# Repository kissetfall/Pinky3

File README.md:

# Pinky3

Pinky3 fork with rotary encoders and kailh hotswaps for thumb row.
This is a WIP, but it's already works great for daily use.

No top/bottom plates are currently available for this board, but it works nice without them.

## Layout

## Firmware

Copy the contents of keymap directory in your qmk/keyboards/pinky/3/keymaps

## TODOs

- [ ] Full choc hotswap support
- [ ] Rework of top, bottom plates, screw holes position.
- [ ] Led strip support
- [ ] Renaming keyboard
- [ ] Build guides, bom, etc.

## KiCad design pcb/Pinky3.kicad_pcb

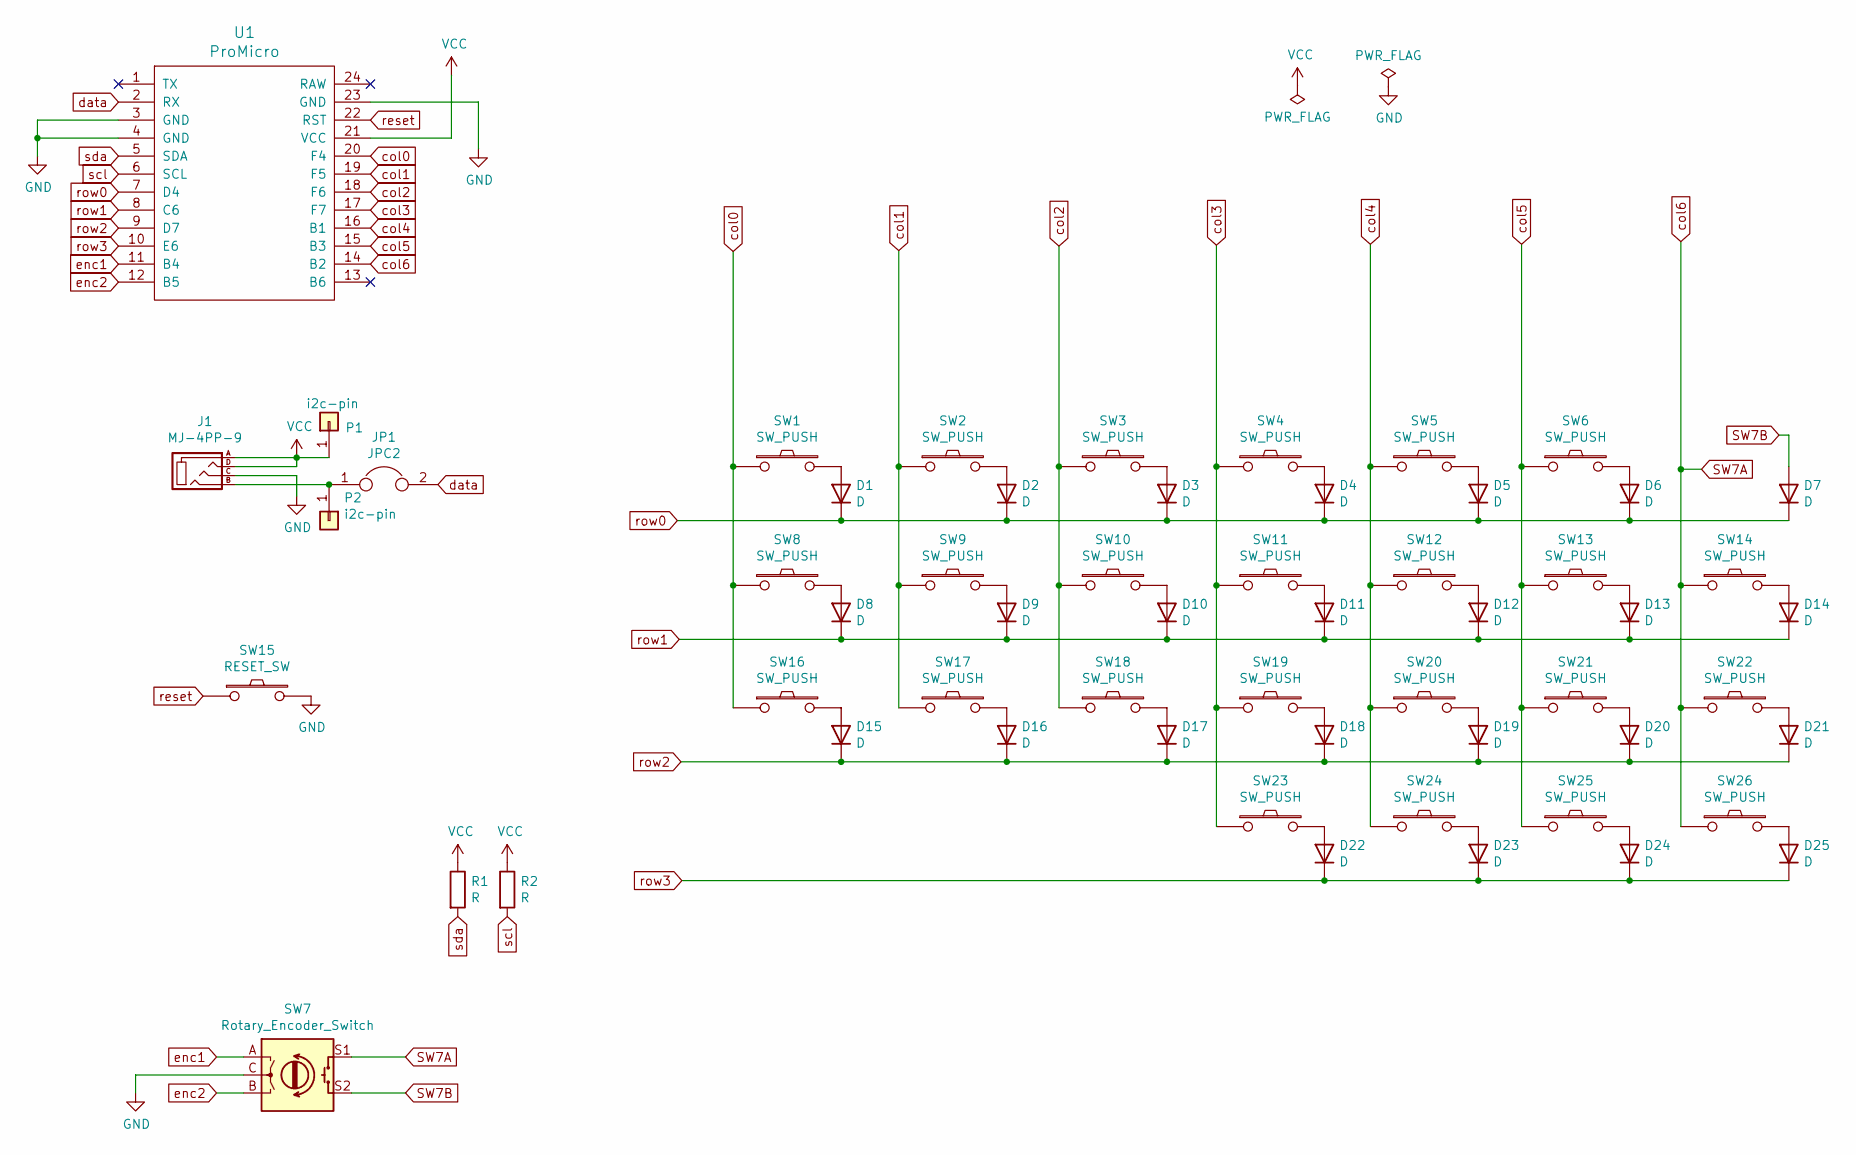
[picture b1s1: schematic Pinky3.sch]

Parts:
D1, D2, D3, D4, D5, D6, D7, D8, D9, D10, D11, D12, D13, D14, D15, D16, D17, D18, D19, D20, D21, D22, D23, D24, D25: D; D3_TH_SMD
J1: MJ-4PP-9
JP1: JPC2
P1, P2: i2c-pin; 1pin_conn
R1, R2: R
SW1, SW2, SW3, SW4, SW5, SW6, SW8, SW9, SW10, SW11, SW12, SW13, SW14, SW16, SW17, SW18, SW19, SW20, SW21, SW22: SW_PUSH; CherryMX_Hotswap
SW7: Rotary_Encoder_Switch; RotaryEncoder_Alps_EC11E-Switch_Vertical_H20mm-keebio_modif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
SW15: RESET_SW; ResetSW
SW23, SW24, SW25, SW26: SW_PUSH; CherryMX_Choc_Hotswap
U1: ProMicro; ProMicro_v2

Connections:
GND: J1.C, SW7.C, SW15.2, U1.3 (GND), U1.4 (GND), U1.23 (GND)
unnamed: D1.2 (A), SW1.2
unnamed: D2.2 (A), SW2.2
unnamed: D3.2 (A), SW3.2
unnamed: D4.2 (A), SW4.2
unnamed: D5.2 (A), SW5.2
unnamed: D6.2 (A), SW6.2
unnamed: D8.2 (A), SW8.2
unnamed: D9.2 (A), SW9.2
unnamed: D10.2 (A), SW10.2
unnamed: D11.2 (A), SW11.2
unnamed: D12.2 (A), SW12.2
unnamed: D13.2 (A), SW13.2
unnamed: D14.2 (A), SW14.2
unnamed: D15.2 (A), SW16.2
unnamed: D16.2 (A), SW17.2
unnamed: D17.2 (A), SW18.2
unnamed: D18.2 (A), SW19.2
unnamed: D19.2 (A), SW20.2
unnamed: D20.2 (A), SW21.2
unnamed: D21.2 (A), SW22.2
unnamed: D22.2 (A), SW23.2
unnamed: D23.2 (A), SW24.2
unnamed: D24.2 (A), SW25.2
unnamed: D25.2 (A), SW26.2
unnamed: J1.B, JP1.1, P2.1
SW7A: SW7.S1, SW14.1, SW22.1, SW26.1, U1.14 (B2)
SW7B: D7.2 (A), SW7.S2
VCC: J1.A, J1.D, P1.1, R1.1, R2.1, U1.21 (VCC)
col0: SW1.1, SW8.1, SW16.1, U1.20 (F4)
col1: SW2.1, SW9.1, SW17.1, U1.19 (F5)
col2: SW3.1, SW10.1, SW18.1, U1.18 (F6)
col3: SW4.1, SW11.1, SW19.1, SW23.1, U1.17 (F7)
col4: SW5.1, SW12.1, SW20.1, SW24.1, U1.16 (B1)
col5: SW6.1, SW13.1, SW21.1, SW25.1, U1.15 (B3)
data: JP1.2, U1.2 (RX)
enc1: SW7.A, U1.11 (B4)
enc2: SW7.B, U1.12 (B5)
reset: SW15.1, U1.22 (RST)
row0: D1.1 (K), D2.1 (K), D3.1 (K), D4.1 (K), D5.1 (K), D6.1 (K), D7.1 (K), U1.7 (D4)
row1: D8.1 (K), D9.1 (K), D10.1 (K), D11.1 (K), D12.1 (K), D13.1 (K), D14.1 (K), U1.8 (C6)
row2: D15.1 (K), D16.1 (K), D17.1 (K), D18.1 (K), D19.1 (K), D20.1 (K), D21.1 (K), U1.9 (D7)
row3: D22.1 (K), D23.1 (K), D24.1 (K), D25.1 (K), U1.10 (E6)
scl: R2.2, U1.6 (SCL)
sda: R1.2, U1.5 (SDA)

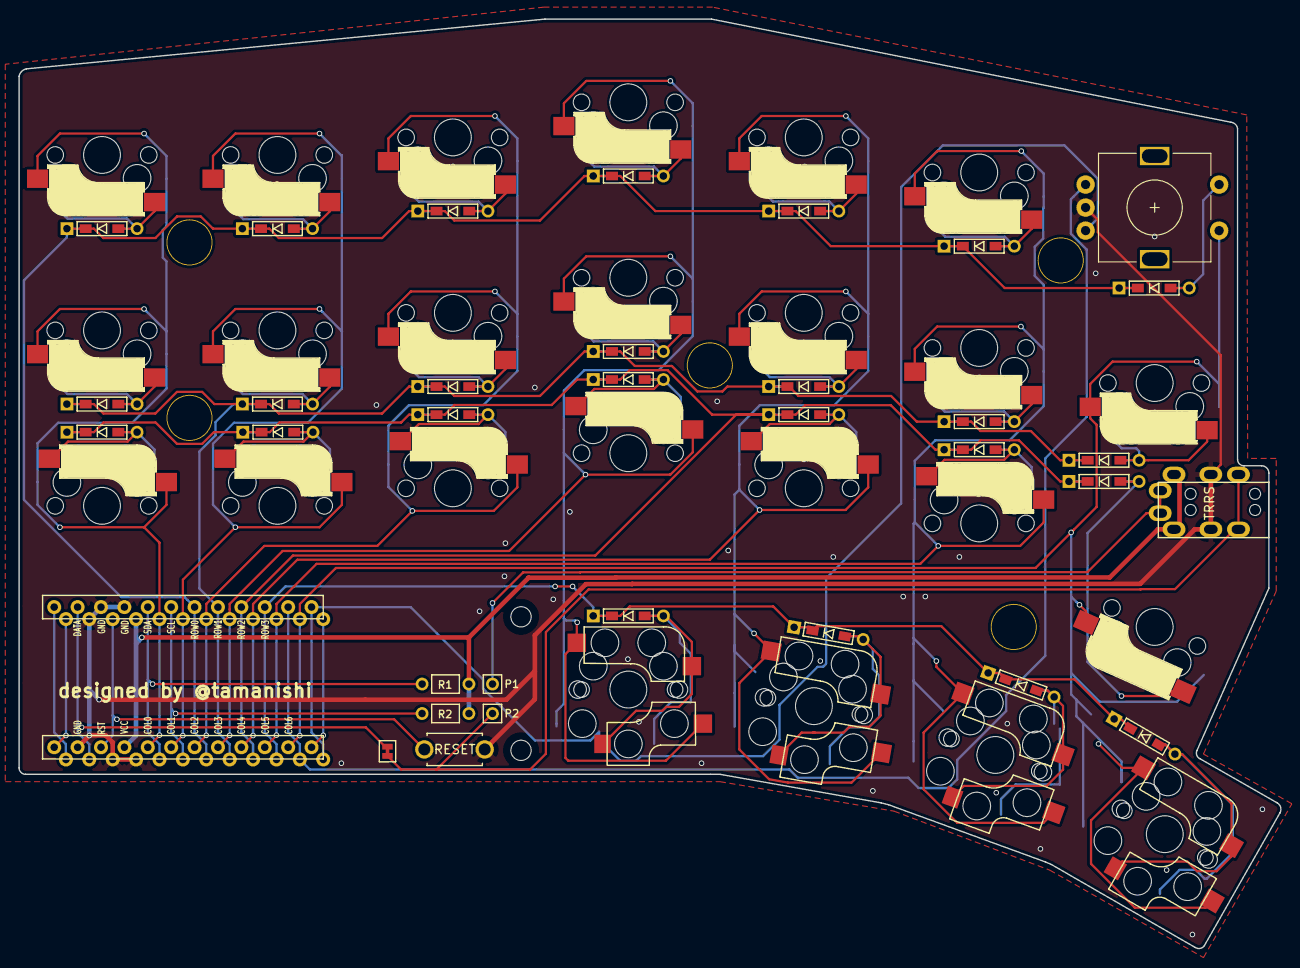
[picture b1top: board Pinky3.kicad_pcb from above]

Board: 2 copper layers, 137.0 x 100.9 mm, 65 parts (0 on the bottom side), 45 nets.

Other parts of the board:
HOLE_M2, HOLE_M2#2: VAL**; HOLE_M2
Ref**: Val**; HOLE
Ref**#2, Ref**#3, Ref**#4, Ref**#5: Val**; HOLE

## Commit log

2021-05-16 full update
